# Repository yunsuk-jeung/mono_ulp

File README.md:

## n36tsu keyboard

- 36 keys
- PG1316S
- nice!view
- nice!nano
- wireless

## TODO

- [x] modify footprints to solder-on
- [x] verify every components orientation
- [x] add text on PCB
- [x] add case holes
- [x] wire components
- [ ] design 3D case

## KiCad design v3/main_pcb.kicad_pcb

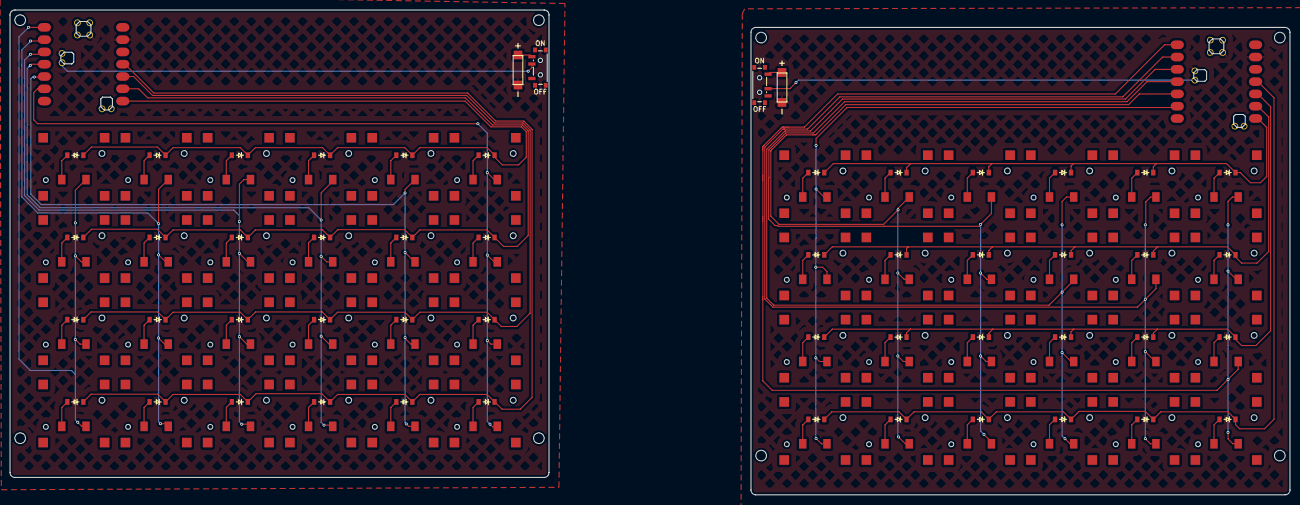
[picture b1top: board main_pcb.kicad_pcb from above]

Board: 2 copper layers, 264.6 x 100.2 mm, 98 parts (0 on the bottom side), 68 nets.

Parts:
D1, D2, D3, D4, D5, D6, D7, D8, D9, D10, D11, D12, D13, D14, D15, D16, D17, D18, D19, D20, D21, D22, D23, D24, D25, D26, D27, D28, D29, D30, D31, D32, D33, D34, D35, D36, D37, D38, D39, D40, D41, D42, D43, D44, D45, D46, D47, D48: diode_tht_sod123
PWR1, PWR2: power_switch_smd_side
S1, S2, S3, S4, S5, S6, S7, S8, S9, S10, S11, S12, S13, S14, S15, S16, S17, S18, S19, S20, S21, S22, S23, S24, S25, S26, S27, S28, S29, S30, S31, S32, S33, S34, S35, S36, S37, S38, S39, S40, S41, S42, S43, S44, S45, S46, S47, S48: CPG1316S01D02_mikeholscher

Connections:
P0: S1.2, S2.2, S3.2, S4.2
P0r: S25.2, S26.2, S27.2, S28.2
P1: S5.2, S6.2, S7.2, S8.2
P1r: S29.2, S30.2, S31.2, S32.2
P2: S9.2, S10.2, S11.2, S12.2
P2r: S33.2, S34.2, S35.2, S36.2
P3: S13.2, S14.2, S15.2, S16.2
P3r: S37.2, S38.2, S39.2, S40.2
P4: S17.2, S18.2, S19.2, S20.2
P4r: S41.2, S42.2, S43.2, S44.2
P5: S21.2, S22.2, S23.2, S24.2
P5r: S45.2, S46.2, S47.2, S48.2
P7: D4.1, D8.1, D12.1, D16.1, D20.1, D24.1
P7r: D28.1, D32.1, D36.1, D40.1, D44.1, D48.1
P8: D3.1, D7.1, D11.1, D15.1, D19.1, D23.1
P8r: D27.1, D31.1, D35.1, D39.1, D43.1, D47.1
P9: D2.1, D6.1, D10.1, D14.1, D18.1, D22.1
P9r: D26.1, D30.1, D34.1, D38.1, D42.1, D46.1
P10: D1.1, D5.1, D9.1, D13.1, D17.1, D21.1
P10r: D25.1, D29.1, D33.1, D37.1, D41.1, D45.1
ecolumn_arow: D11.2, S11.1
ecolumn_qrow: D12.2, S12.1
ecolumn_thumb_row: D9.2, S9.1
ecolumn_zrow: D10.2, S10.1
mirror_ecolumn_arow: D35.2, S35.1
mirror_ecolumn_qrow: D36.2, S36.1
mirror_ecolumn_thumb_row: D33.2, S33.1
mirror_ecolumn_zrow: D34.2, S34.1
mirror_qcolumn_arow: D27.2, S27.1
mirror_qcolumn_qrow: D28.2, S28.1
mirror_qcolumn_thumb_row: D25.2, S25.1
mirror_qcolumn_zrow: D26.2, S26.1
mirror_rcolumn_arow: D39.2, S39.1
mirror_rcolumn_qrow: D40.2, S40.1
mirror_rcolumn_thumb_row: D37.2, S37.1
mirror_rcolumn_zrow: D38.2, S38.1
mirror_tcolumn_arow: D43.2, S43.1
mirror_tcolumn_qrow: D44.2, S44.1
mirror_tcolumn_thumb_row: D41.2, S41.1
mirror_tcolumn_zrow: D42.2, S42.1
mirror_wcolumn_arow: D31.2, S31.1
mirror_wcolumn_qrow: D32.2, S32.1
mirror_wcolumn_thumb_row: D29.2, S29.1
mirror_wcolumn_zrow: D30.2, S30.1
mirror_ycolumn_arow: D47.2, S47.1
mirror_ycolumn_qrow: D48.2, S48.1
mirror_ycolumn_thumb_row: D45.2, S45.1
mirror_ycolumn_zrow: D46.2, S46.1
qcolumn_arow: D3.2, S3.1
qcolumn_qrow: D4.2, S4.1
qcolumn_thumb_row: D1.2, S1.1
qcolumn_zrow: D2.2, S2.1
rcolumn_arow: D15.2, S15.1
rcolumn_qrow: D16.2, S16.1
rcolumn_thumb_row: D13.2, S13.1
rcolumn_zrow: D14.2, S14.1
tcolumn_arow: D19.2, S19.1
tcolumn_qrow: D20.2, S20.1
tcolumn_thumb_row: D17.2, S17.1
tcolumn_zrow: D18.2, S18.1
wcolumn_arow: D7.2, S7.1
wcolumn_qrow: D8.2, S8.1
wcolumn_thumb_row: D5.2, S5.1
wcolumn_zrow: D6.2, S6.1
ycolumn_arow: D23.2, S23.1
ycolumn_qrow: D24.2, S24.1
ycolumn_thumb_row: D21.2, S21.1
ycolumn_zrow: D22.2, S22.1

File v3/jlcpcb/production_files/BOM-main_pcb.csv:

Comment,Designator,Footprint,LCSC,Quantity
,D11,diode_tht_sod123,,1
,D10,diode_tht_sod123,,1
,D15,diode_tht_sod123,,1
,S11,CPG1316S01D02_mikeholscher,,1
,D20,diode_tht_sod123,,1
,D5,diode_tht_sod123,,1
,S20,CPG1316S01D02_mikeholscher,,1
,D6,diode_tht_sod123,,1
,D23,diode_tht_sod123,,1
,S9,CPG1316S01D02_mikeholscher,,1
,D9,diode_tht_sod123,,1
,S2,CPG1316S01D02_mikeholscher,,1
,S14,CPG1316S01D02_mikeholscher,,1
,D4,diode_tht_sod123,,1
,S1,CPG1316S01D02_mikeholscher,,1
,S21,CPG1316S01D02_mikeholscher,,1
,S3,CPG1316S01D02_mikeholscher,,1
,S17,CPG1316S01D02_mikeholscher,,1
,D24,diode_tht_sod123,,1
,D14,diode_tht_sod123,,1
,D7,diode_tht_sod123,,1
,D13,diode_tht_sod123,,1
,D21,diode_tht_sod123,,1
,D1,diode_tht_sod123,,1
,S5,CPG1316S01D02_mikeholscher,,1
,S19,CPG1316S01D02_mikeholscher,,1
,PWR1,power_switch_smd_side,,1
,S12,CPG1316S01D02_mikeholscher,,1
,D16,diode_tht_sod123,,1
,D22,diode_tht_sod123,,1
,S24,CPG1316S01D02_mikeholscher,,1
,D3,diode_tht_sod123,,1
,D18,diode_tht_sod123,,1
,D17,diode_tht_sod123,,1
,S22,CPG1316S01D02_mikeholscher,,1
,D19,diode_tht_sod123,,1
,S15,CPG1316S01D02_mikeholscher,,1
,S4,CPG1316S01D02_mikeholscher,,1
,S8,CPG1316S01D02_mikeholscher,,1
,S6,CPG1316S01D02_mikeholscher,,1
,S10,CPG1316S01D02_mikeholscher,,1
,D2,diode_tht_sod123,,1
,S23,CPG1316S01D02_mikeholscher,,1
,S7,CPG1316S01D02_mikeholscher,,1
,D8,diode_tht_sod123,,1
,S13,CPG1316S01D02_mikeholscher,,1
,S16,CPG1316S01D02_mikeholscher,,1
,D12,diode_tht_sod123,,1
,S18,CPG1316S01D02_mikeholscher,,1

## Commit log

2024-12-08 Add ergogen configuration
2024-12-10 Update PG1316 footprint
2024-12-10 Modify ergogen config.yaml
2024-12-11 Modify ergogen yaml
2024-12-11 Add README, kicad and image
2024-12-12 Adjust PCB component positions
2024-12-12 Add text footprint
2024-12-14 Remove pcb border
2024-12-14 Route left PCB
2024-12-16 Modify routing
2024-12-17 Complete PCB wiring
2024-12-17 Update PCB wiring (DRC)
2024-12-19 Modify PCB
2025-01-07 Update PCB image
2025-01-19 Add images
2025-02-25 starting for mono ulp
2025-02-26 fix bin/bash
2025-02-26 added center points
2025-02-27 changed outline
2025-02-28 added reset switch
2025-02-28 added footprint for battery
2025-03-01 fixed battery_pad
2025-03-01 added screw
2025-03-01 smooth layout
2025-03-02 added case outline
2025-03-05 trying split
2025-03-05 need better idea
2025-03-05 maybe the best
2025-03-05 without stagger
2025-03-09 better than before
2025-03-12 added footprints and changed layout
2026-03-29 final
